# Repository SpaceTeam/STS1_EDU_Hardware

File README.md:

# STS1_EDU_Hardware
 Contains all Hardware Informations from EDU 2.6 onwards

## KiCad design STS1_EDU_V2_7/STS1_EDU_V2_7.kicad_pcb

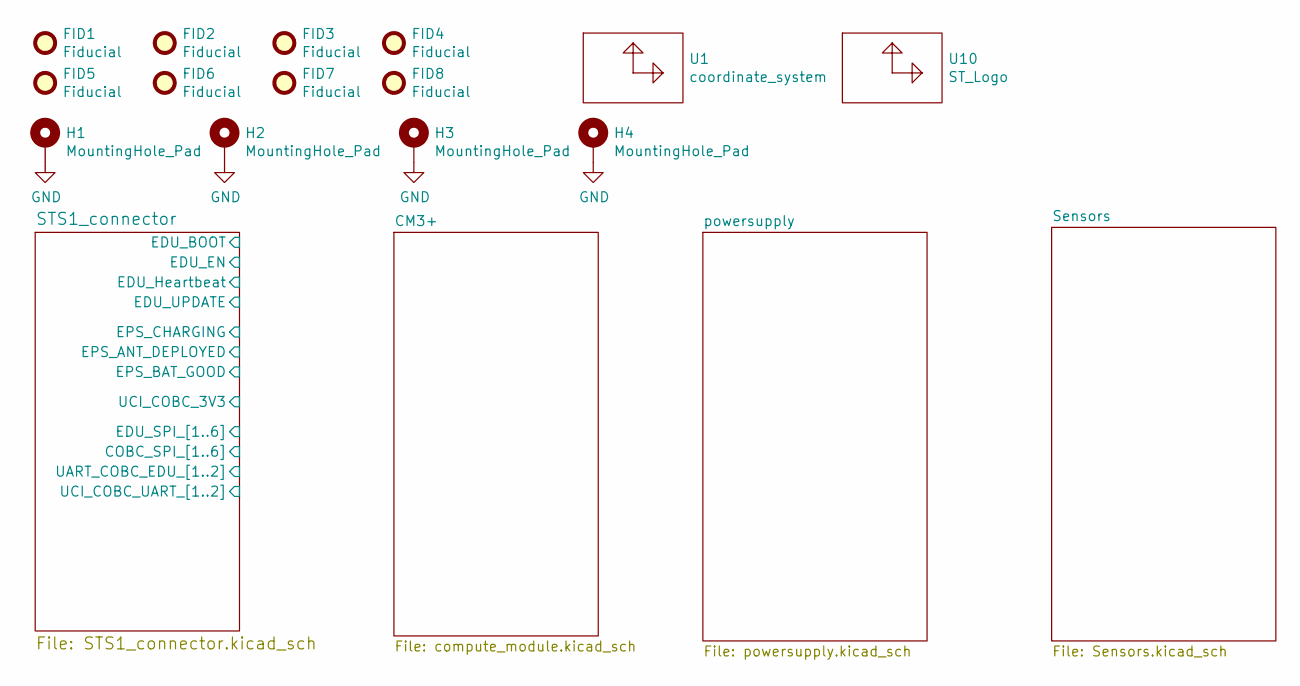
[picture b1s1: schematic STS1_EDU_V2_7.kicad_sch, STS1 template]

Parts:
FID1, FID2, FID3, FID4, FID5, FID6, FID7, FID8: Fiducial; Fiducial_0.75mm_Mask1.5mm
H1, H2, H3, H4: MountingHole_Pad; MountingHole_4.3mm_M4_Pad_Via
U1: coordinate_system; Coordinates
U10: ST_Logo; STLogo_7x8

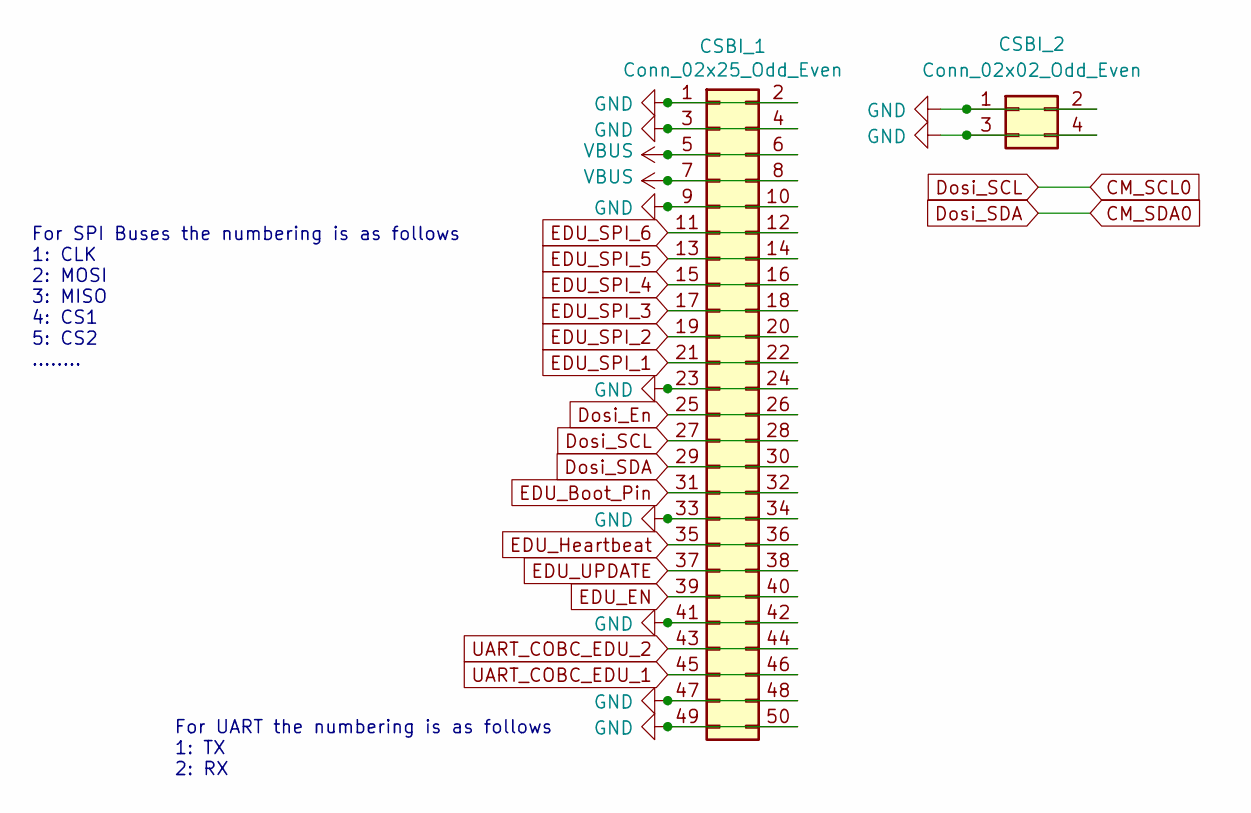
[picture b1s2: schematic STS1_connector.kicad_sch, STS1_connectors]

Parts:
CSBI_1: Conn_02x25_Odd_Even; PinHeader_2x25_P2.00mm_Vertical
CSBI_2: Conn_02x02_Odd_Even; PinHeader_2x02_P2.00mm_Vertical

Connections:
CM_SCL0: CSBI_1.27, CSBI_1.28; also elsewhere on the board
CM_SDA0: CSBI_1.29, CSBI_1.30; also elsewhere on the board
Dosi_En: CSBI_1.25, CSBI_1.26; also elsewhere on the board
EDU_Boot_Pin: CSBI_1.31, CSBI_1.32; also elsewhere on the board
EDU_EN: CSBI_1.39, CSBI_1.40; also elsewhere on the board
EDU_Heartbeat: CSBI_1.35, CSBI_1.36; also elsewhere on the board
EDU_SPI_1: CSBI_1.21, CSBI_1.22; also elsewhere on the board
EDU_SPI_2: CSBI_1.19, CSBI_1.20; also elsewhere on the board
EDU_SPI_3: CSBI_1.17, CSBI_1.18; also elsewhere on the board
EDU_SPI_4: CSBI_1.15, CSBI_1.16; also elsewhere on the board
EDU_SPI_5: CSBI_1.13, CSBI_1.14; also elsewhere on the board
EDU_SPI_6: CSBI_1.11, CSBI_1.12; also elsewhere on the board
EDU_UPDATE: CSBI_1.37, CSBI_1.38; also elsewhere on the board
UART_COBC_EDU_1: CSBI_1.45, CSBI_1.46
UART_COBC_EDU_2: CSBI_1.43, CSBI_1.44
VBUS: CSBI_1.5, CSBI_1.6, CSBI_1.7, CSBI_1.8; also elsewhere on the board

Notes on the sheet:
For SPI Buses the numbering is as follows 1: CLK 2: MOSI 3: MISO 4: CS1 5: CS2 ........
For UART the numbering is as follows 1: TX 2: RX

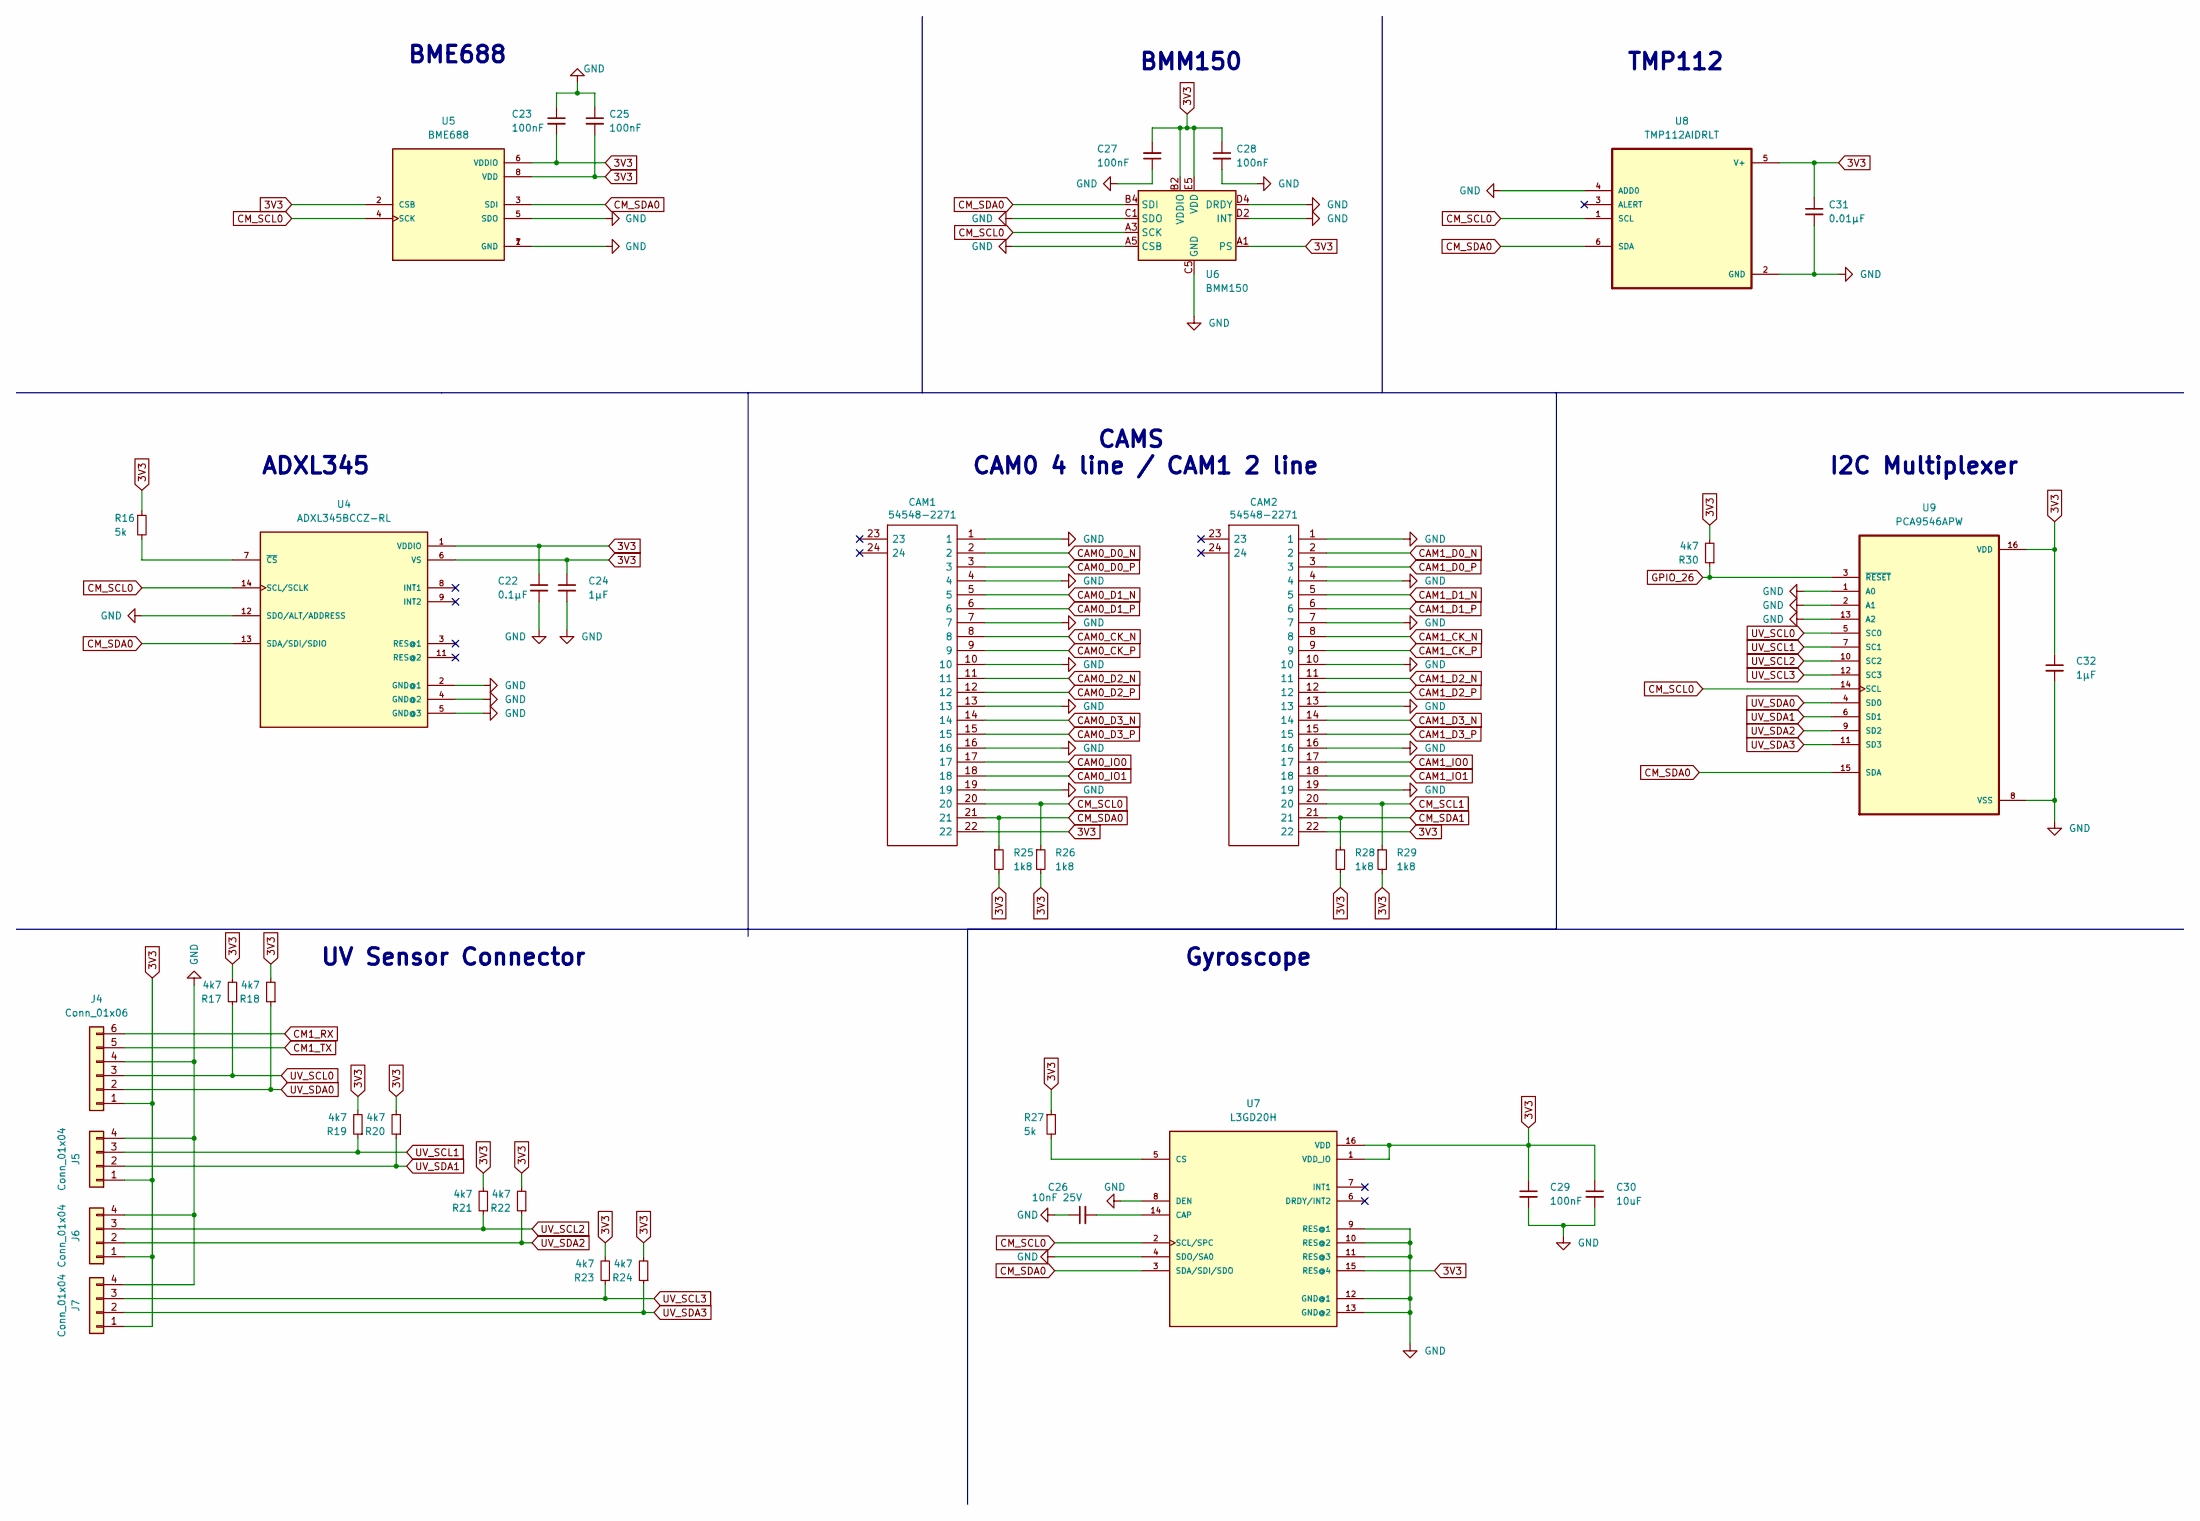
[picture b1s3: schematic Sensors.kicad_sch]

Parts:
C22: 0.1µF; C_0603_1608Metric_Pad1.08x0.95mm_HandSolder
C23, C25, C27, C28, C29: 100nF; C_0603_1608Metric_Pad1.08x0.95mm_HandSolder
C24, C32: 1µF; C_0603_1608Metric_Pad1.08x0.95mm_HandSolder
C26: 10nF 25V; C_0603_1608Metric_Pad1.08x0.95mm_HandSolder
C30: 10uF; C_0603_1608Metric_Pad1.08x0.95mm_HandSolder
C31: 0.01µF; C_0603_1608Metric_Pad1.08x0.95mm_HandSolder
CAM1, CAM2: 54548-2271; 545482271; Manufacturer_Part_Number 54548-2271; Mouser Part Number 538-54548-2271
J4: Conn_01x06; Molex_200528-0060_1x06-1MP_P1.00mm_Horizontal
J5, J6, J7: Conn_01x04; Molex_200528-0040_1x04-1MP_P1.00mm_Horizontal
R16, R27: 5k; R_0603_1608Metric_Pad0.98x0.95mm_HandSolder
R17, R18, R19, R20, R21, R22, R23, R24, R30: 4k7; R_0603_1608Metric_Pad0.98x0.95mm_HandSolder
R25, R26, R28, R29: 1k8; R_0603_1608Metric_Pad0.98x0.95mm_HandSolder
U4: ADXL345BCCZ-RL; LGA-14_3x5mm_P0.8mm_LayoutBorder1x6y
U5: BME688; Bosch_LGA-8_3x3mm_P0.8mm_ClockwisePinNumbering; PARTREV 1.0
U6: BMM150; WLCSP-12_1.56x1.56mm_P0.4mm
U7: L3GD20H; LGA-16_3x3mm_P0.5mm_LayoutBorder3x5y
U8: TMP112AIDRLT; SOT-563
U9: PCA9546APW; TSSOP-16_4.4x5mm_P0.65mm

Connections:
3V3: C22.1, C23.2, C24.1, C25.2, C27.2, C28.1, C29.1, C30.1, C31.1, C32.1, CAM1.22, CAM2.22, J4.1, J5.1, J6.1, J7.1, R16.1, R17.2, R18.2, R19.2, R20.2, R21.2, R22.2, R23.2, R24.2, R25.2, R26.2, R27.1, R28.2, R29.2, R30.2, U4.1 (VDDIO), U4.6 (VS), U5.2 (CSB), U5.6 (VDDIO), U5.8 (VDD), U6.A1 (PS), U6.B2 (VDDIO), U6.E5 (VDD), U7.1 (VDD_IO), U7.15 (RES@4), U7.16 (VDD), U8.5 (V+), U9.16 (VDD); also elsewhere on the board
CAM0_CK_N: CAM1.8; also elsewhere on the board
CAM0_CK_P: CAM1.9; also elsewhere on the board
CAM0_D0_N: CAM1.2; also elsewhere on the board
CAM0_D0_P: CAM1.3; also elsewhere on the board
CAM0_D1_N: CAM1.5; also elsewhere on the board
CAM0_D1_P: CAM1.6; also elsewhere on the board
CAM0_D2_N: CAM1.11
CAM0_D2_P: CAM1.12
CAM0_D3_N: CAM1.14
CAM0_D3_P: CAM1.15
CAM0_IO0: CAM1.17; also elsewhere on the board
CAM0_IO1: CAM1.18; also elsewhere on the board
CAM1_CK_N: CAM2.8; also elsewhere on the board
CAM1_CK_P: CAM2.9; also elsewhere on the board
CAM1_D0_N: CAM2.2; also elsewhere on the board
CAM1_D0_P: CAM2.3; also elsewhere on the board
CAM1_D1_N: CAM2.5; also elsewhere on the board
CAM1_D1_P: CAM2.6; also elsewhere on the board
CAM1_D2_N: CAM2.11; also elsewhere on the board
CAM1_D2_P: CAM2.12; also elsewhere on the board
CAM1_D3_N: CAM2.14; also elsewhere on the board
CAM1_D3_P: CAM2.15; also elsewhere on the board
CAM1_IO0: CAM2.17; also elsewhere on the board
CAM1_IO1: CAM2.18; also elsewhere on the board
CM1_RX: J4.6; also elsewhere on the board
CM1_TX: J4.5; also elsewhere on the board
CM_SCL0: CAM1.20, R26.1, U4.14 (SCL/SCLK), U5.4 (SCK), U6.A3 (SCK), U7.2 (SCL/SPC), U8.1 (SCL), U9.14 (SCL); also elsewhere on the board
CM_SCL1: CAM2.20, R29.1; also elsewhere on the board
CM_SDA0: CAM1.21, R25.1, U4.13 (SDA/SDI/SDIO), U5.3 (SDI), U6.B4 (SDI), U7.3 (SDA/SDI/SDO), U8.6 (SDA), U9.15 (SDA); also elsewhere on the board
CM_SDA1: CAM2.21, R28.1; also elsewhere on the board
GPIO_26: R30.1, U9.3 (~RESET); also elsewhere on the board
unnamed: R16.2, U4.7 (~CS)
unnamed: C26.2, U7.14 (CAP)
unnamed: R27.2, U7.5 (CS)
UV_SCL0: J4.3, R17.1, U9.5 (SC0)
UV_SCL1: J5.3, R19.1, U9.7 (SC1)
UV_SCL2: J6.3, R21.1, U9.10 (SC2)
UV_SCL3: J7.3, R23.1, U9.12 (SC3)
UV_SDA0: J4.2, R18.1, U9.4 (SD0)
UV_SDA1: J5.2, R20.1, U9.6 (SD1)
UV_SDA2: J6.2, R22.1, U9.9 (SD2)
UV_SDA3: J7.2, R24.1, U9.11 (SD3)

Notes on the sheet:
Gyroscope
BME688
CAMS CAM0 4 line / CAM1 2 line
I2C Multiplexer
ADXL345
UV Sensor Connector
TMP112
BMM150

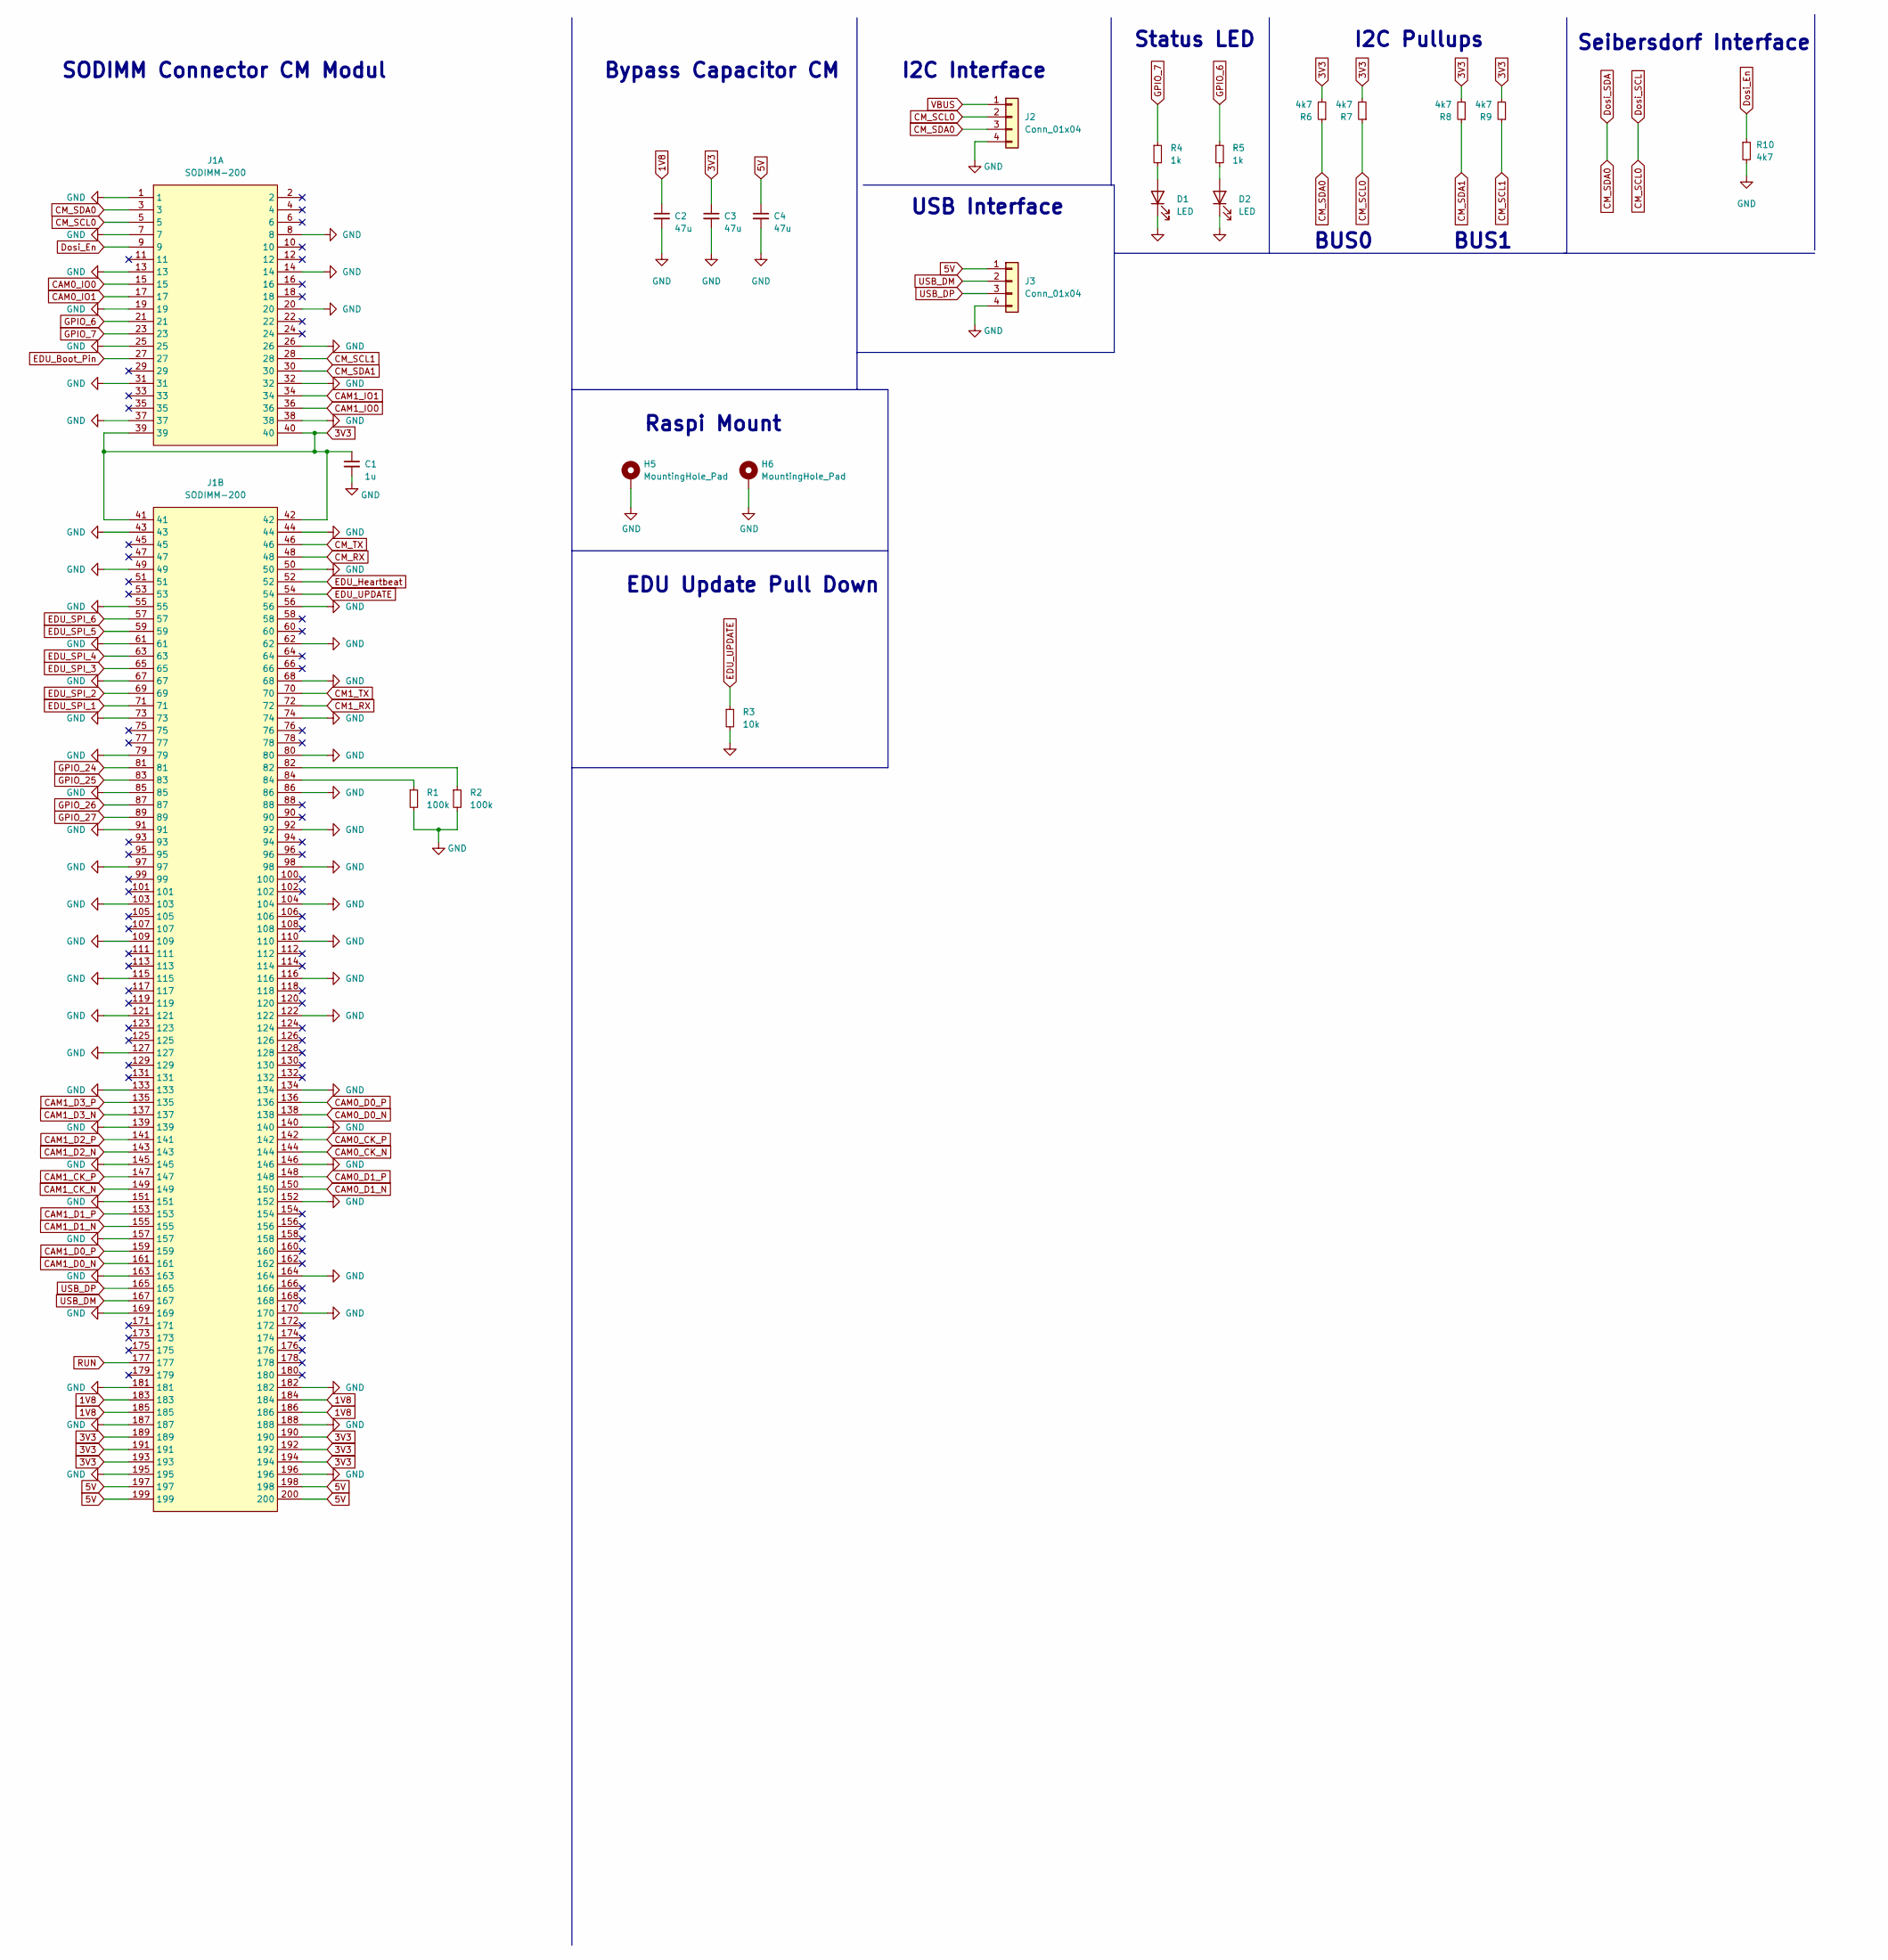
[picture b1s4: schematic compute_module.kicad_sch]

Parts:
C1: 1u; C_0603_1608Metric_Pad1.08x0.95mm_HandSolder
C2, C3, C4: 47u; C_0603_1608Metric_Pad1.08x0.95mm_HandSolder
D1, D2: LED; LED_0603_1608Metric_Pad1.05x0.95mm_HandSolder
H5, H6: MountingHole_Pad; MountingHole_2.2mm_M2_Pad_Via
J1: SODIMM-200; 17172544
J2, J3: Conn_01x04; PinHeader_1x04_P2.54mm_Vertical
R1, R2: 100k; R_0603_1608Metric_Pad0.98x0.95mm_HandSolder
R3: 10k; R_0603_1608Metric_Pad0.98x0.95mm_HandSolder
R4, R5: 1k; R_0603_1608Metric_Pad0.98x0.95mm_HandSolder
R6, R7, R8, R9, R10: 4k7; R_0603_1608Metric_Pad0.98x0.95mm_HandSolder

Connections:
1V8: C2.1, J1.183, J1.184, J1.185, J1.186; also elsewhere on the board
3V3: C1.1, C3.1, J1.39, J1.40, J1.41, J1.42, J1.189, J1.190, J1.191, J1.192, J1.193, J1.194, R6.2, R7.2, R8.2, R9.2; also elsewhere on the board
5V: C4.1, J1.197, J1.198, J1.199, J1.200, J3.1; also elsewhere on the board
CAM0_CK_N: J1.144; also elsewhere on the board
CAM0_CK_P: J1.142; also elsewhere on the board
CAM0_D0_N: J1.138; also elsewhere on the board
CAM0_D0_P: J1.136; also elsewhere on the board
CAM0_D1_N: J1.150; also elsewhere on the board
CAM0_D1_P: J1.148; also elsewhere on the board
CAM0_IO0: J1.15; also elsewhere on the board
CAM0_IO1: J1.17; also elsewhere on the board
CAM1_CK_N: J1.149; also elsewhere on the board
CAM1_CK_P: J1.147; also elsewhere on the board
CAM1_D0_N: J1.161; also elsewhere on the board
CAM1_D0_P: J1.159; also elsewhere on the board
CAM1_D1_N: J1.155; also elsewhere on the board
CAM1_D1_P: J1.153; also elsewhere on the board
CAM1_D2_N: J1.143; also elsewhere on the board
CAM1_D2_P: J1.141; also elsewhere on the board
CAM1_D3_N: J1.137; also elsewhere on the board
CAM1_D3_P: J1.135; also elsewhere on the board
CAM1_IO0: J1.36; also elsewhere on the board
CAM1_IO1: J1.34; also elsewhere on the board
CM1_RX: J1.72; also elsewhere on the board
CM1_TX: J1.70; also elsewhere on the board
CM_RX: J1.48
CM_SCL0: J1.5, J2.2, R7.1; also elsewhere on the board
CM_SCL1: J1.28, R9.1; also elsewhere on the board
CM_SDA0: J1.3, J2.3, R6.1; also elsewhere on the board
CM_SDA1: J1.30, R8.1; also elsewhere on the board
CM_TX: J1.46
Dosi_En: J1.9, R10.1; also elsewhere on the board
EDU_Boot_Pin: J1.27; also elsewhere on the board
EDU_Heartbeat: J1.52; also elsewhere on the board
EDU_SPI_1: J1.71; also elsewhere on the board
EDU_SPI_2: J1.69; also elsewhere on the board
EDU_SPI_3: J1.65; also elsewhere on the board
EDU_SPI_4: J1.63; also elsewhere on the board
EDU_SPI_5: J1.59; also elsewhere on the board
EDU_SPI_6: J1.57; also elsewhere on the board
EDU_UPDATE: J1.54, R3.1; also elsewhere on the board
GPIO_6: J1.21, R5.1
GPIO_7: J1.23, R4.1
GPIO_24: J1.81
GPIO_25: J1.83
GPIO_26: J1.87; also elsewhere on the board
GPIO_27: J1.89
unnamed: D1.2 (A), R4.2
unnamed: D2.2 (A), R5.2
unnamed: J1.82, R2.1
unnamed: J1.84, R1.1
RUN: J1.177
USB_DM: J1.167, J3.2
USB_DP: J1.165, J3.3
VBUS: J2.1; also elsewhere on the board

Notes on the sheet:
SODIMM Connector CM Modul
EDU Update Pull Down
Seibersdorf Interface
BUS0
Status LED
USB Interface
Raspi Mount
BUS1
I2C Pullups
Bypass Capacitor CM
I2C Interface

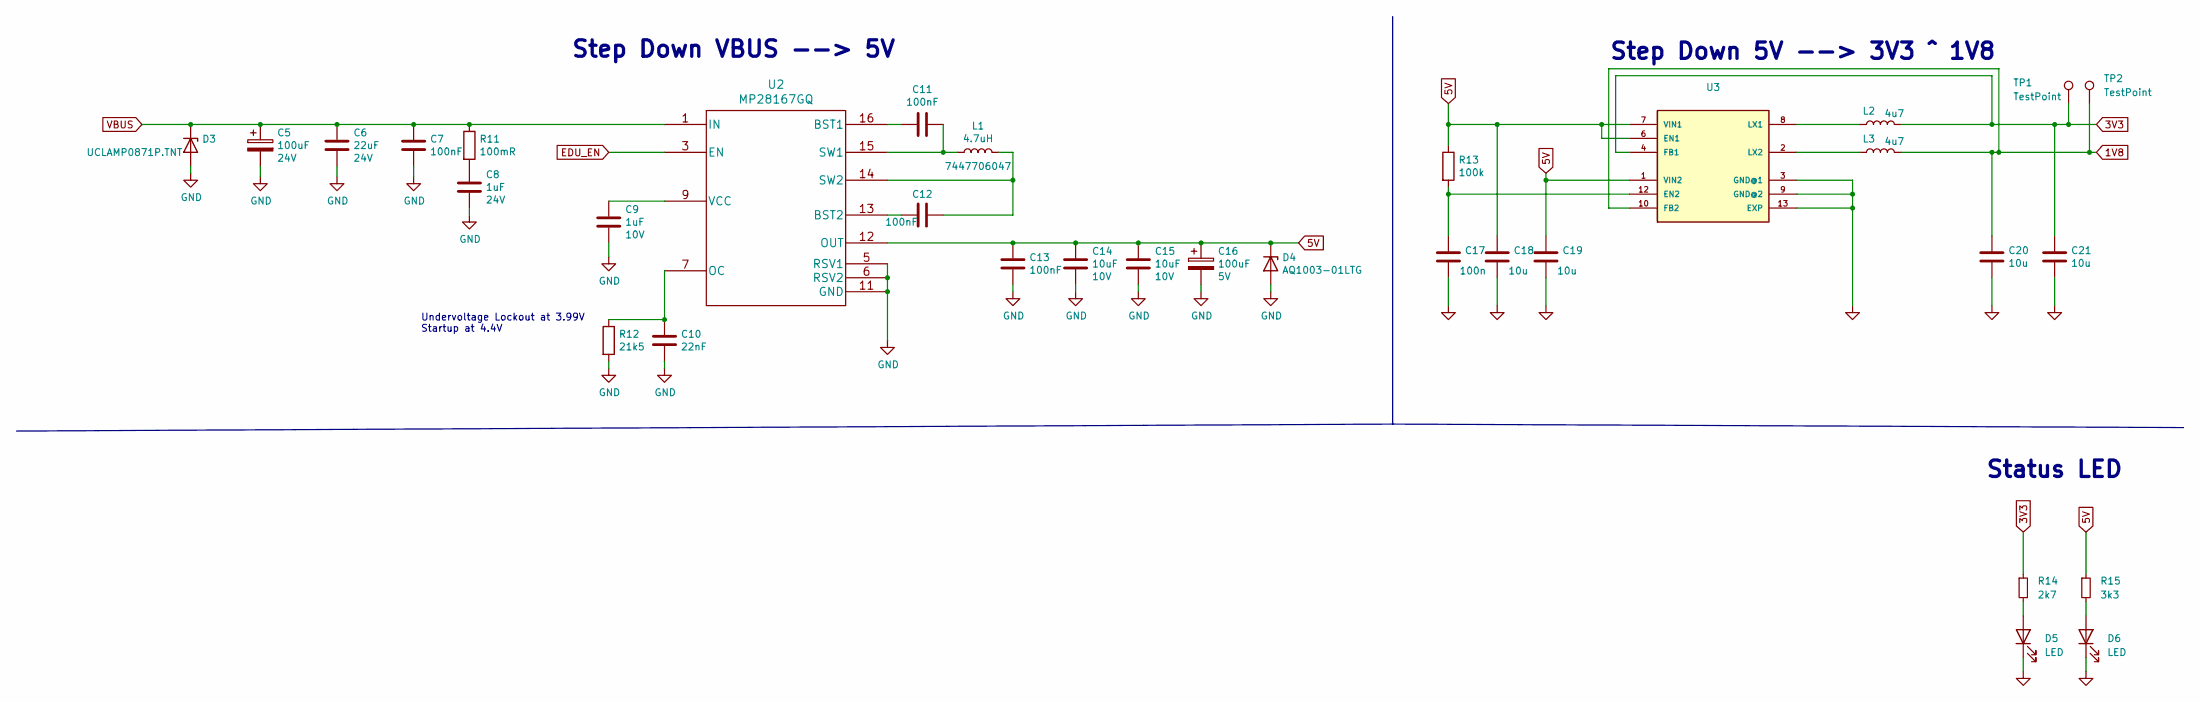
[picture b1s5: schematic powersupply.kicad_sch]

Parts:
C5: 100uF; CP_EIA-7343-43_Kemet-X; Voltage 24V
C6: 22uF; C_1206_3216Metric; Voltage 24V
C7, C11, C12, C13: 100nF; C_0603_1608Metric
C8: 1uF; C_0805_2012Metric; Voltage 24V
C9: 1uF; C_0805_2012Metric; Voltage 10V
C10: 22nF; C_0603_1608Metric
C14, C15: 10uF; C_0805_2012Metric; Voltage 10V
C16: 100uF; CP_EIA-7343-43_Kemet-X; Voltage 5V
C17: 100n; C_0603_1608Metric_Pad1.08x0.95mm_HandSolder
C18, C19, C20, C21: 10u; C_0603_1608Metric_Pad1.08x0.95mm_HandSolder
D3: UCLAMP0871P.TNT; SGP1610N2
D4: AQ1003-01LTG; D_SOD-523
D5, D6: LED; LED_0603_1608Metric_Pad1.05x0.95mm_HandSolder
L1: 4.7uH; L_12x12mm_H6mm; Part 7447706047
L2, L3: 4u7; L_1210_3225Metric_Pad1.42x2.65mm_HandSolder
R11: 100mR; R_0603_1608Metric
R12: 21k5; R_0603_1608Metric
R13: 100k; R_0603_1608Metric_Pad0.98x0.95mm_HandSolder
R14: 2k7; R_0603_1608Metric_Pad0.98x0.95mm_HandSolder
R15: 3k3; R_0603_1608Metric_Pad0.98x0.95mm_HandSolder
TP1, TP2: TestPoint; TestPoint_Pad_1.0x1.0mm
U2: MP28167GQ; MP28167_QFN16
U3: SON45P300X300X80-13N

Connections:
1V8: C20.1, L3.2, TP2.1, U3.10 (FB2); also elsewhere on the board
3V3: C21.1, L2.2, R14.1, TP1.1, U3.4 (FB1); also elsewhere on the board
5V: C13.1, C14.1, C15.1, C16.1, C18.1, C19.1, D4.1 (K), R13.1, R15.1, U2.12 (OUT), U3.1 (VIN2), U3.6 (EN1), U3.7 (VIN1); also elsewhere on the board
EDU_EN: U2.3 (EN); also elsewhere on the board
unnamed: C8.1, R11.2
unnamed: D5.2 (A), R14.2
unnamed: D6.2 (A), R15.2
unnamed: C11.2, U2.16 (BST1)
unnamed: C12.2, U2.13 (BST2)
unnamed: C10.1, R12.1, U2.7 (OC)
unnamed: C11.1, L1.1, U2.15 (SW1)
unnamed: C12.1, L1.2, U2.14 (SW2)
unnamed: C9.1, U2.9 (VCC)
unnamed: C17.1, R13.2, U3.12 (EN2)
unnamed: L2.1, U3.8 (LX1)
unnamed: L3.1, U3.2 (LX2)
VBUS: C5.1, C6.1, C7.1, D3.1 (K), R11.1, U2.1 (IN); also elsewhere on the board

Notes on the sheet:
Status LED
Step Down VBUS --> 5V
Undervoltage Lockout at 3.99V Startup at 4.4V
Step Down 5V --> 3V3 ^ 1V8

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
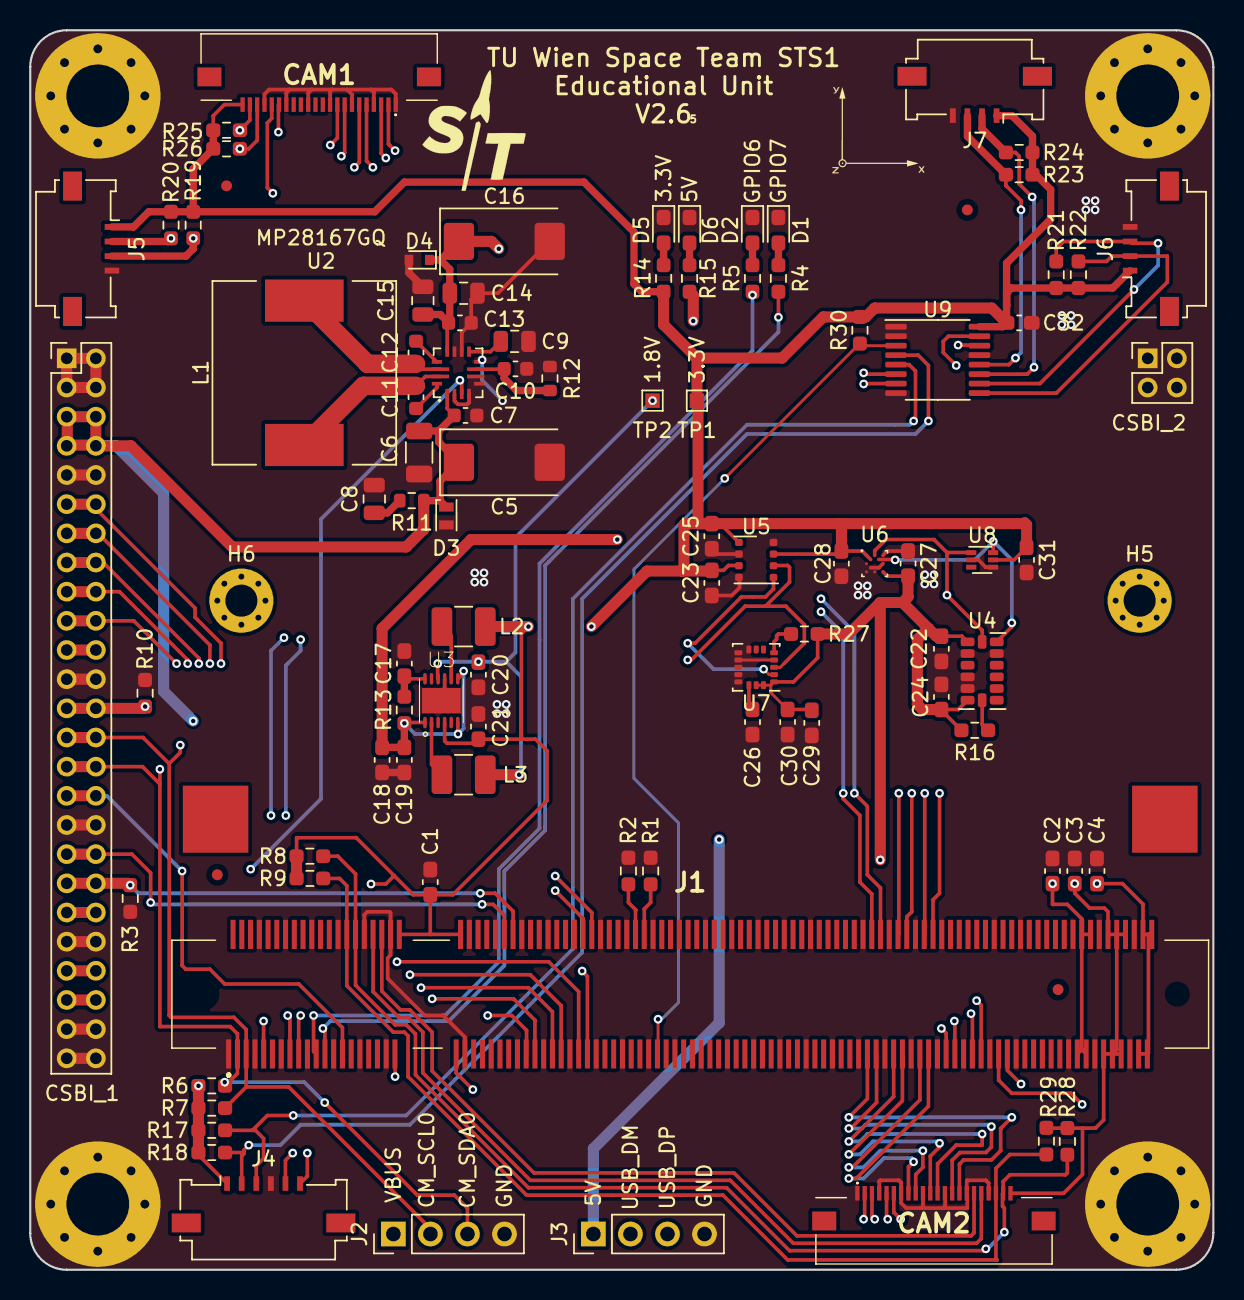
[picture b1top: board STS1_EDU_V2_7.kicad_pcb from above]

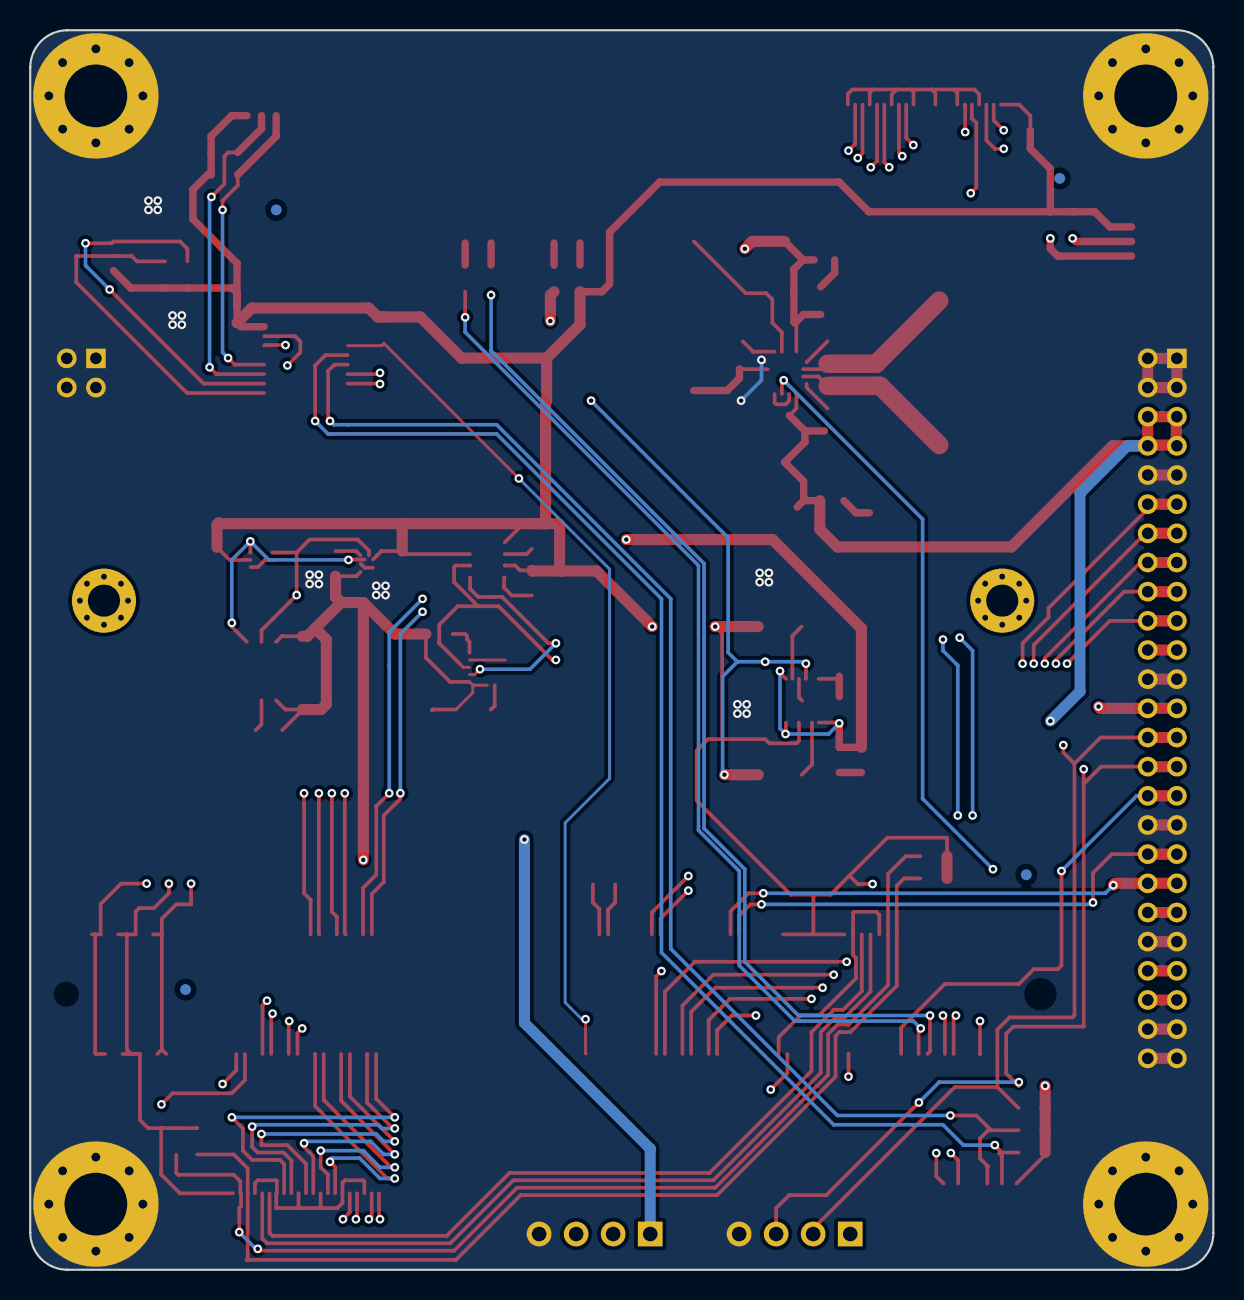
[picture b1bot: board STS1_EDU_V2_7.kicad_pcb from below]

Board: 4 copper layers, 81.1 x 85.0 mm, 108 parts (4 on the bottom side), 77 nets.
